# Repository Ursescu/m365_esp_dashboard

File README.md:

# M365 Dashboard replacement

## Description

Replacement for BLE m365 scooter dashboard using ESP32 chip.

## Build

Clone official esp-idf sdk repo and set `IDF_PATH` environment variable
to point it.

```bash
    git clone --recursive https://github.com/espressif/esp-idf.git ~/esp-idf

    cd ~/esp-idf && ./install.sh && . ./export.sh
```

Build app and watch the info using `make`.

```bash
    make flash monitor
```

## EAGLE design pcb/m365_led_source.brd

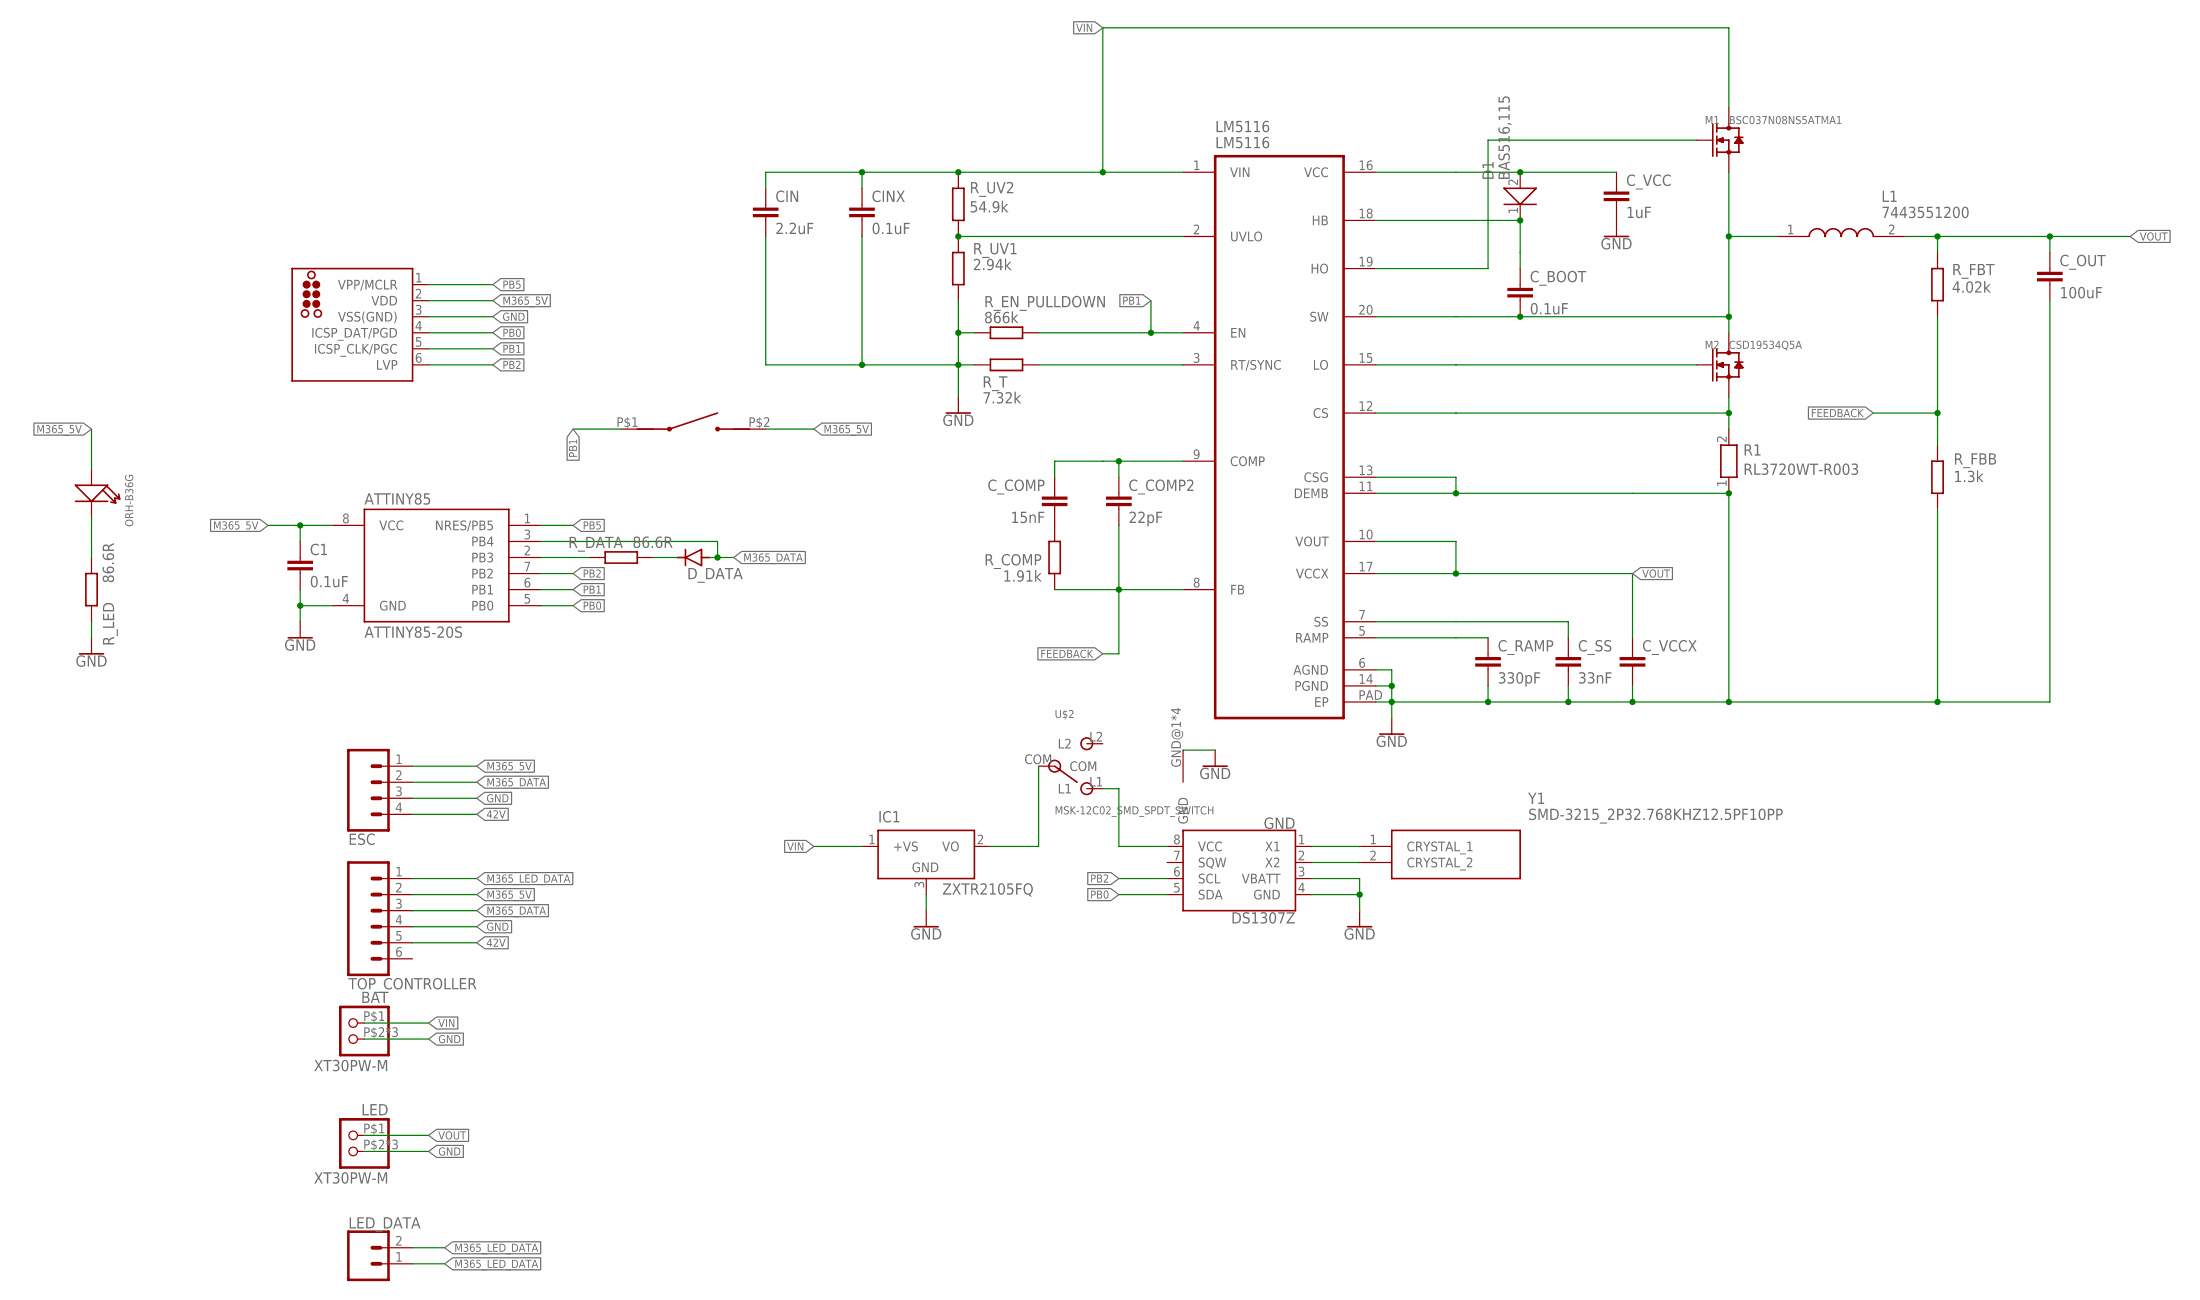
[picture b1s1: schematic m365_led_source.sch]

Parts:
ATTINY85: ATTINY85-20S; SOIC8_EIAJ_208MIL
BAT: XT30PW-M
C1: 0.1uF; C0402
CIN: 2.2uF; C1210
CINX: 0.1uF; C0603
C_BOOT: 0.1uF; C0603
C_COMP: 15nF; C1005
C_COMP2: 22pF; C0402
C_OUT: 100uF; C1210
C_RAMP: 330pF; C0402
C_SS: 33nF; C0402
C_VCC: 1uF; C0402
C_VCCX: CC0402; C0402
D1: BAS516,115; SOD1608X65N
D_DATA: SMAFJ75A
ESC: CONN_04LONGPADS; 1X04_LONGPADS
GND: DS1307Z; SO08-0.15
IC1: ZXTR2105FQ; SOT23
J2: TC2030-MCP-NL
L1: 7443551200; WE-HCI_1350/136523
LED: XT30PW-M
LED_DATA: CONN_02PTH3; 1X02_LONGPADS
LM5116: LM5116; TSSOP20-PAD
M1: BSC037N08NS5ATMA1; CSD19531Q5AT
M2: CSD19534Q5A; CSD19531Q5AT
R1: RL3720WT-R003; RESC2038X70N
R_COMP: 1.91k; R0402
R_DATA: 86.6R; R0402
R_EN_PULLDOWN: 866k; R0402
R_FBB: 1.3k; R1206
R_FBT: 4.02k; R1206
R_LED: 86.6R; R0402
R_T: 7.32k; R0402
R_UV1: 2.94k; R0402
R_UV2: 54.9k; R0402
TINY_LED: ORH-B36G; LED-0603
TOP_CONTROLLER: CONN_06LONGPADS; 1X06_LONGPADS
U$1: TL3302BF260QJ
U$2: MSK-12C02_SMD_SPDT_SWITCH; MSK-12C02
Y1: SMD-3215_2P32.768KHZ12.5PF10PP; SMD3215_2P32768KHZ125PF10PPM

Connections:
5V_REG: IC1.2 (VO), U$2.COM
42V: ESC.4, TOP_CONTROLLER.5
FEEDBACK: C_COMP2.2, LM5116.8 (FB), R_COMP.1, R_FBB.2, R_FBT.1
GND: ATTINY85.4 (GND), BAT.P$2 (2), BAT.P$3 (2), BAT.P$4 (2), C1.2, CIN.2, CINX.2, C_OUT.2, C_RAMP.2, C_SS.2, C_VCC.2, C_VCCX.2, ESC.3, GND.3 (VBATT), GND.4 (GND), IC1.3 (GND), J2.3 (VSS(GND)), LED.P$2 (2), LED.P$3 (2), LED.P$4 (2), LM5116.6 (AGND), LM5116.11 (DEMB), LM5116.13 (CSG), LM5116.14 (PGND), LM5116.PAD (EP), R1.1, R_EN_PULLDOWN.1, R_FBB.1, R_LED.1, R_T.1, R_UV1.1, TOP_CONTROLLER.4, U$2.GND@1 (GND), U$2.GND@2 (GND), U$2.GND@3 (GND), U$2.GND@4 (GND)
M365_5V: ATTINY85.8 (VCC), C1.1, ESC.1, J2.2 (VDD), TINY_LED.+, TOP_CONTROLLER.2, U$1.P$2
M365_DATA: ATTINY85.3 (PB4), D_DATA.P$2 (ANODE), ESC.2, TOP_CONTROLLER.3
M365_LED_DATA: LED_DATA.1, LED_DATA.2, TOP_CONTROLLER.1
unnamed: C_COMP.2, R_COMP.2
unnamed: LM5116.2 (UVLO), R_UV1.2, R_UV2.1
unnamed: GND.8 (VCC), U$2.L1
unnamed: LM5116.3 (RT/SYNC), R_T.2
unnamed: C_COMP.1, C_COMP2.1, LM5116.9 (COMP)
unnamed: GND.1 (X1), Y1.1 (CRYSTAL_1)
unnamed: C_SS.1, LM5116.7 (SS)
unnamed: C_RAMP.1, LM5116.5 (RAMP)
unnamed: R_LED.2, TINY_LED.-
unnamed: D_DATA.P$1 (CATHODE), R_DATA.2
unnamed: GND.2 (X2), Y1.2 (CRYSTAL_2)
unnamed: LM5116.12 (CS), M2.1 (S), M2.2 (S), M2.3 (S), R1.2
unnamed: LM5116.15 (LO), M2.4 (G)
unnamed: C_BOOT.2, L1.1, LM5116.20 (SW), M1.1 (S), M1.2 (S), M1.3 (S), M2.5 (D), M2.6 (D), M2.7 (D), M2.8 (D), M2.9 (D)
unnamed: LM5116.19 (HO), M1.4 (G)
unnamed: C_BOOT.1, D1.1, LM5116.18 (HB)
unnamed: C_VCC.1, D1.2, LM5116.16 (VCC)
PB0: ATTINY85.5 (PB0), GND.5 (SDA), J2.4 (ICSP_DAT/PGD)
PB1: ATTINY85.6 (PB1), J2.5 (ICSP_CLK/PGC), LM5116.4 (EN), R_EN_PULLDOWN.2, U$1.P$1
PB2: ATTINY85.7 (PB2), GND.6 (SCL), J2.6 (LVP)
PB3: ATTINY85.2 (PB3), R_DATA.1
PB5: ATTINY85.1 (NRES/PB5), J2.1 (VPP/MCLR)
VIN: BAT.P$1 (1), CIN.1, CINX.1, IC1.1 (+VS), LM5116.1 (VIN), M1.5 (D), M1.6 (D), M1.7 (D), M1.8 (D), M1.9 (D), R_UV2.2
VOUT: C_OUT.1, C_VCCX.1, L1.2, LED.P$1 (1), LM5116.10 (VOUT), LM5116.17 (VCCX), R_FBT.2

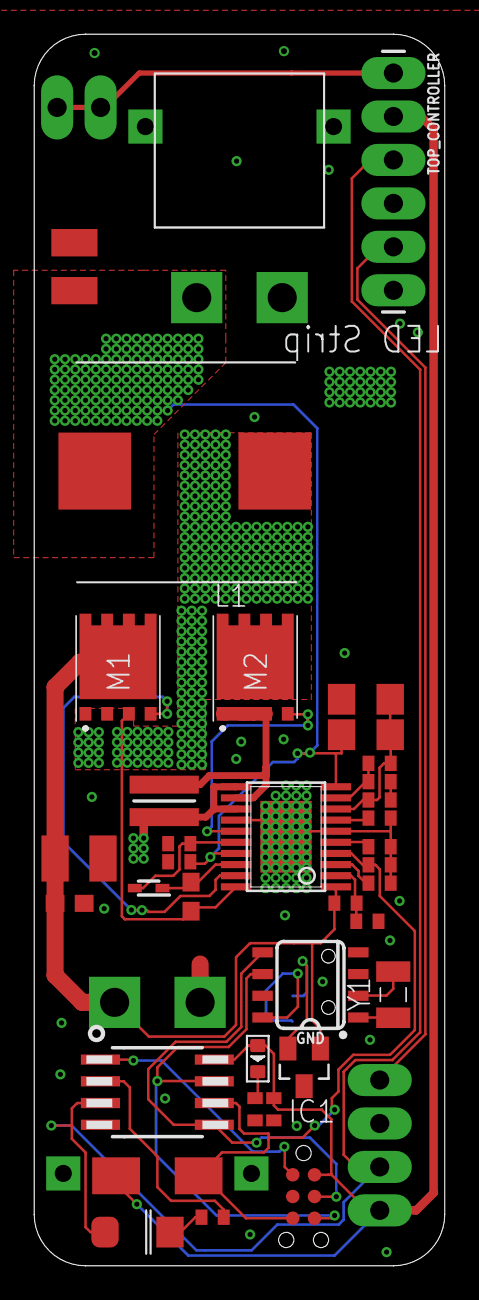
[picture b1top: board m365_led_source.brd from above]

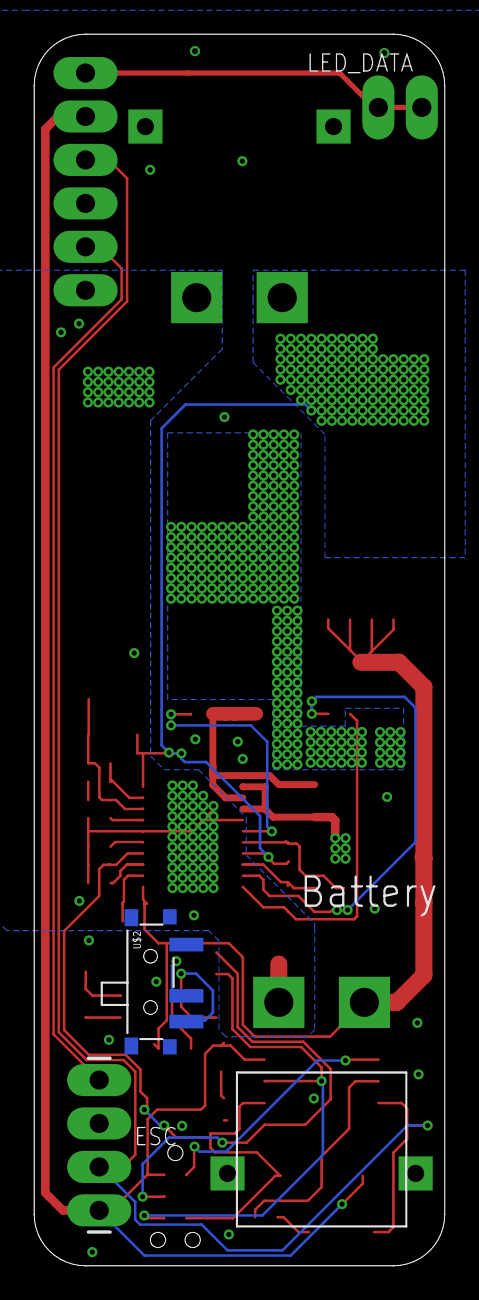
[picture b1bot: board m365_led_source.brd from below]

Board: 2 copper layers, 24.0 x 72.0 mm, 40 parts (4 on the bottom side), 31 nets.

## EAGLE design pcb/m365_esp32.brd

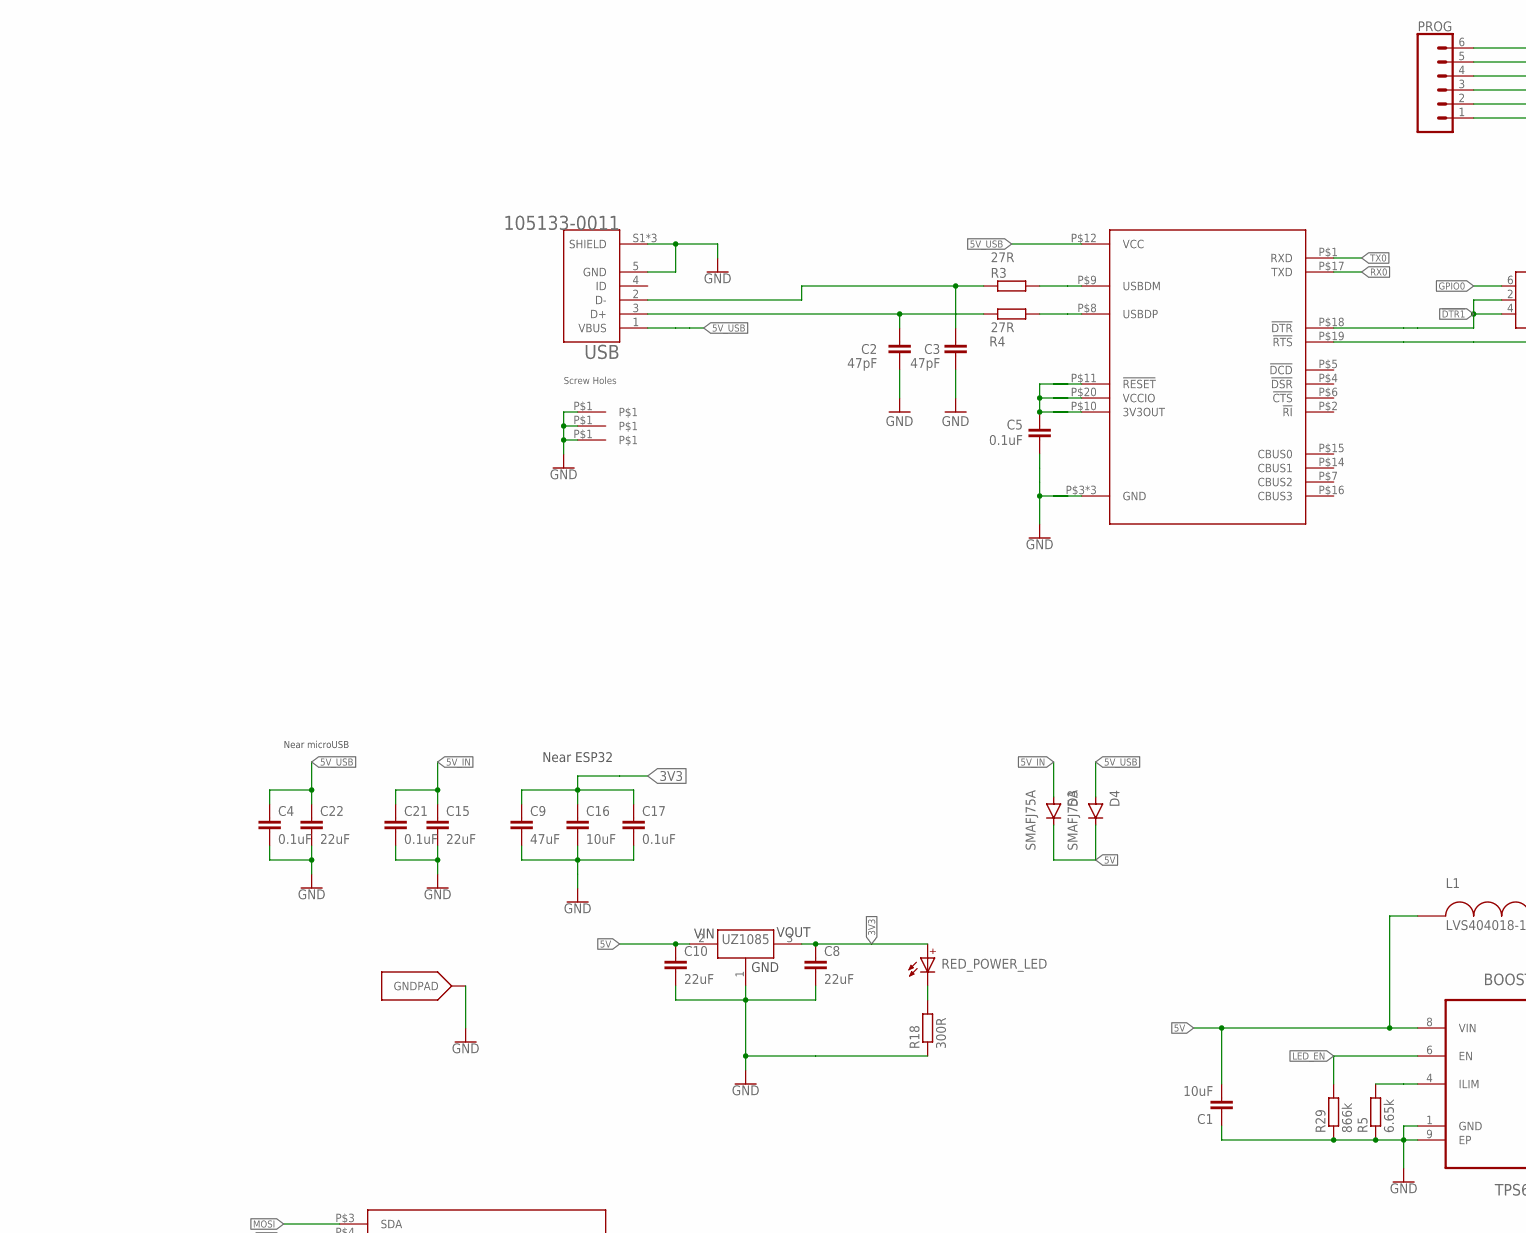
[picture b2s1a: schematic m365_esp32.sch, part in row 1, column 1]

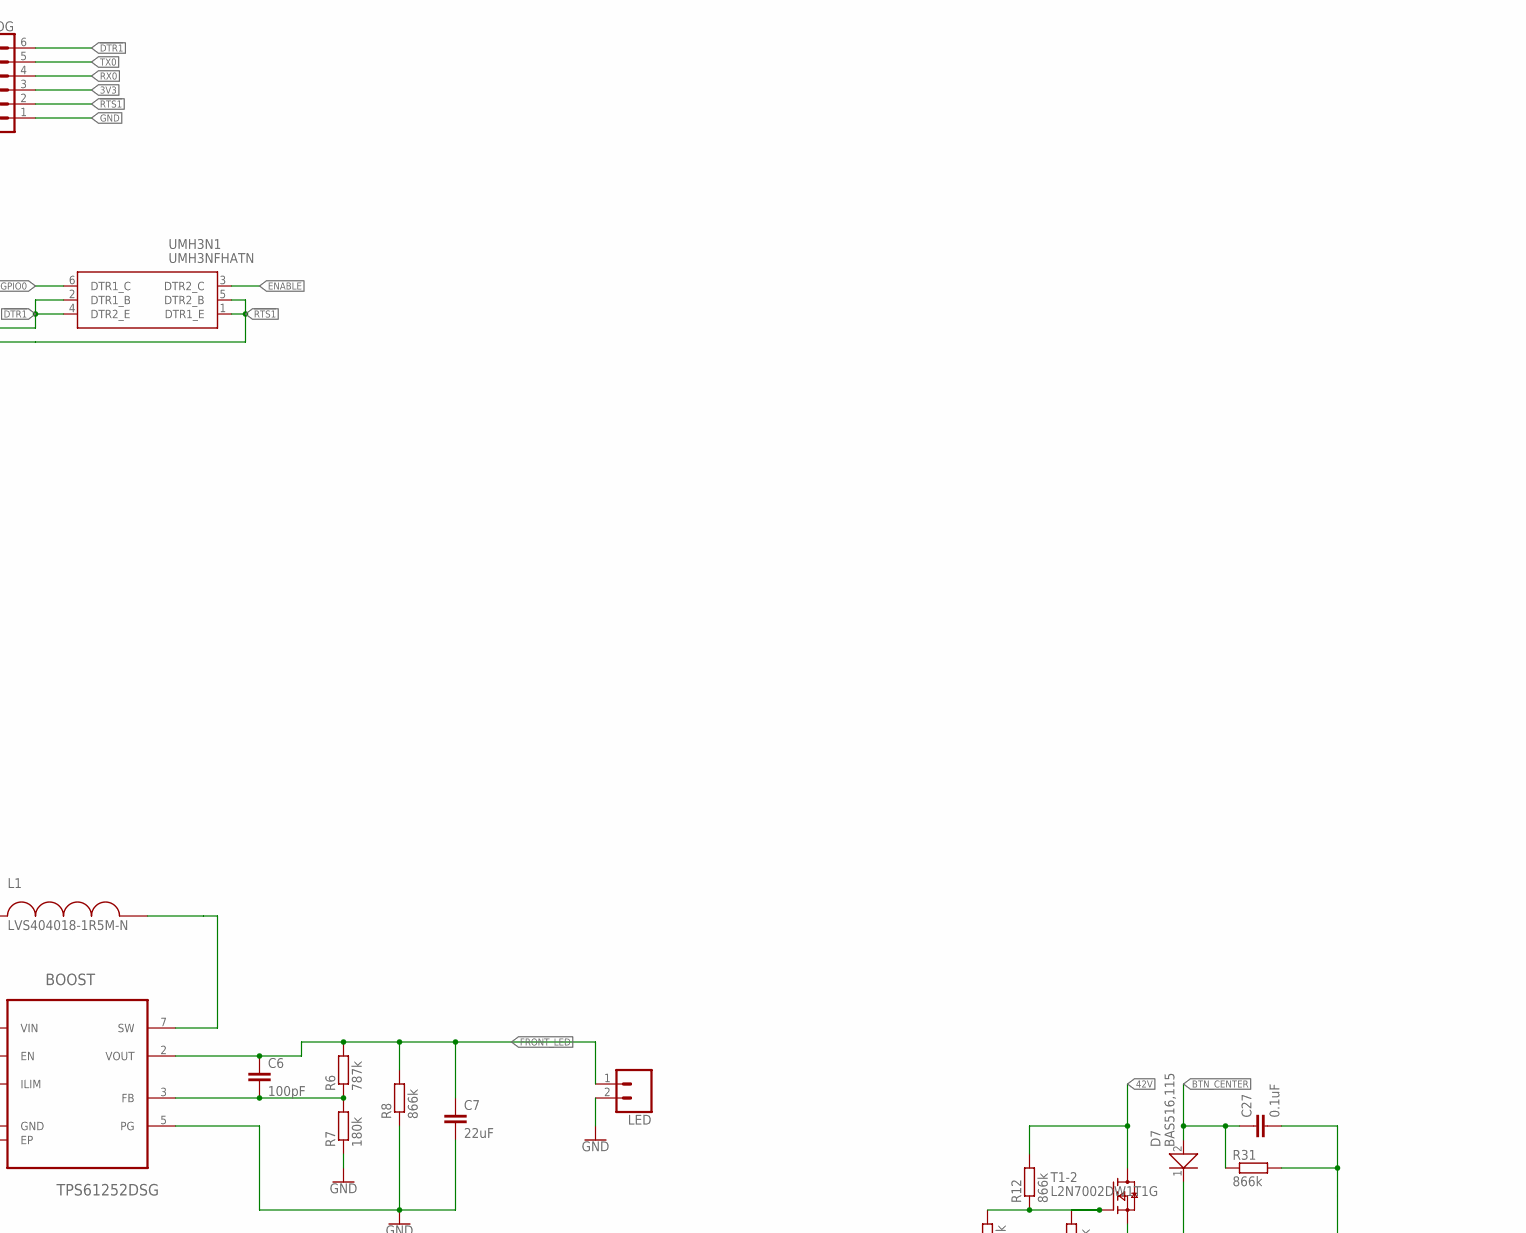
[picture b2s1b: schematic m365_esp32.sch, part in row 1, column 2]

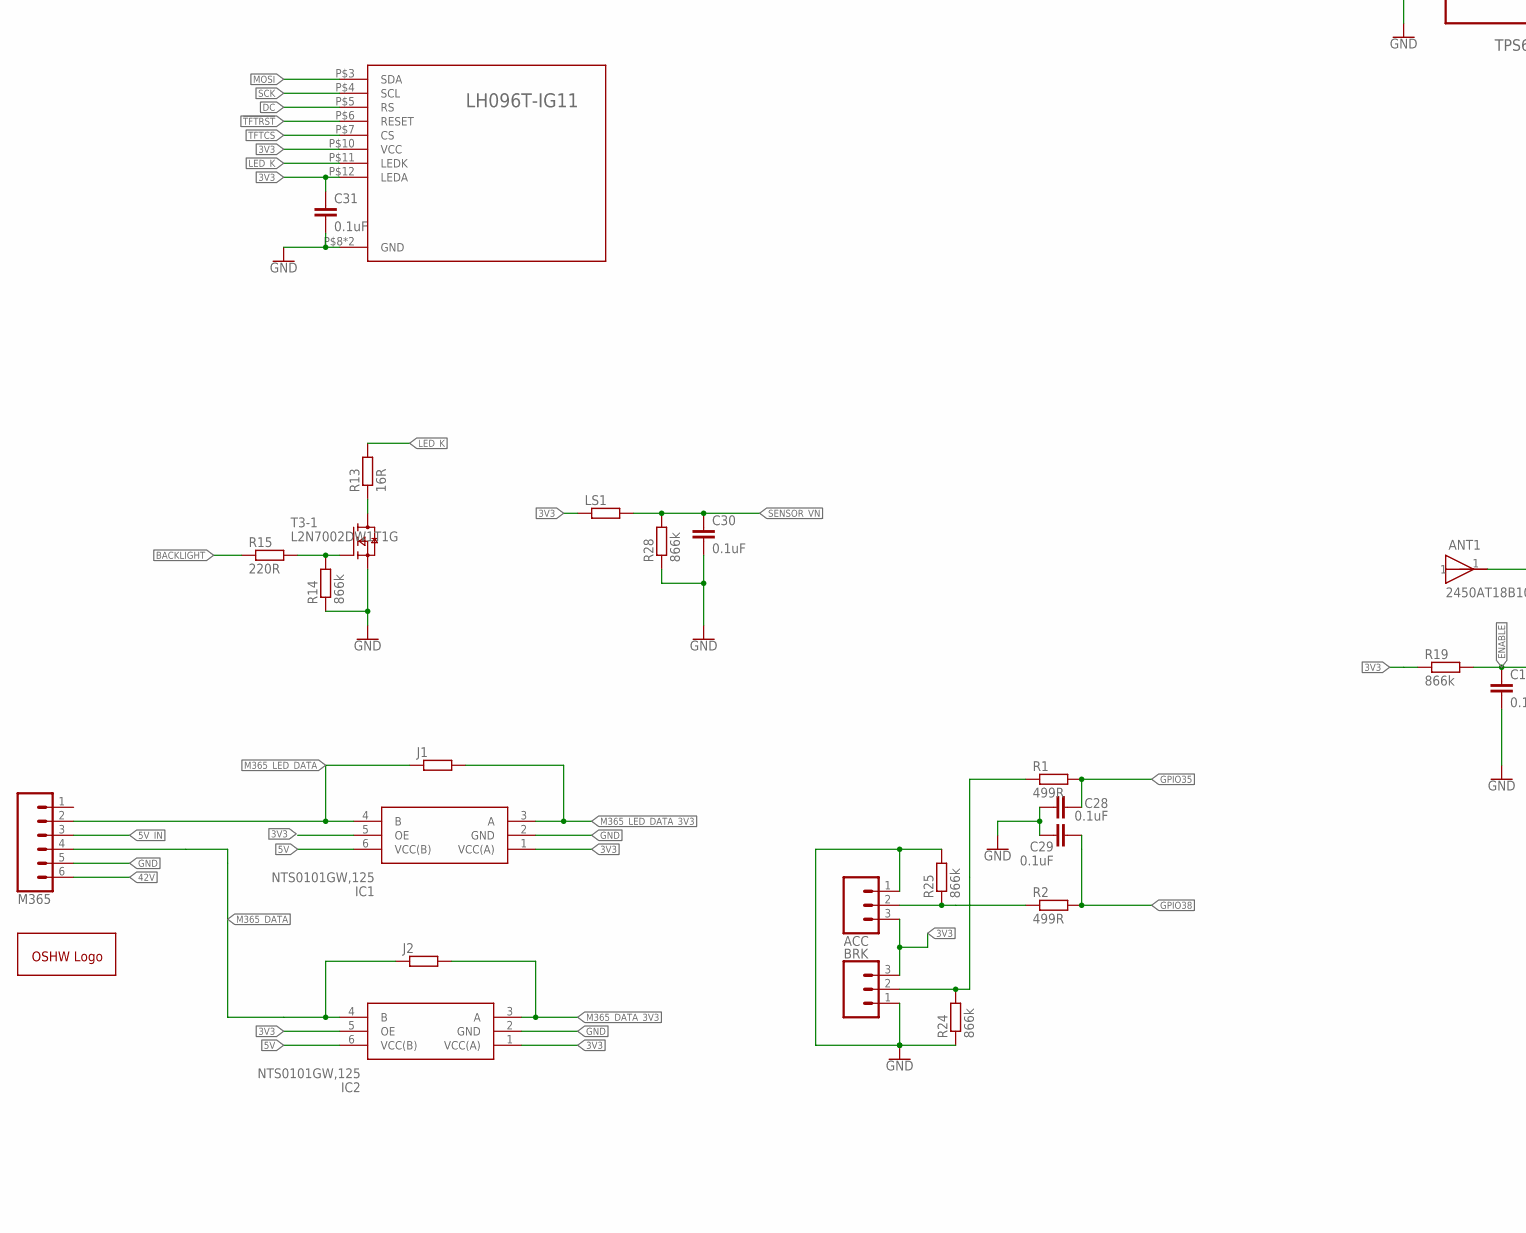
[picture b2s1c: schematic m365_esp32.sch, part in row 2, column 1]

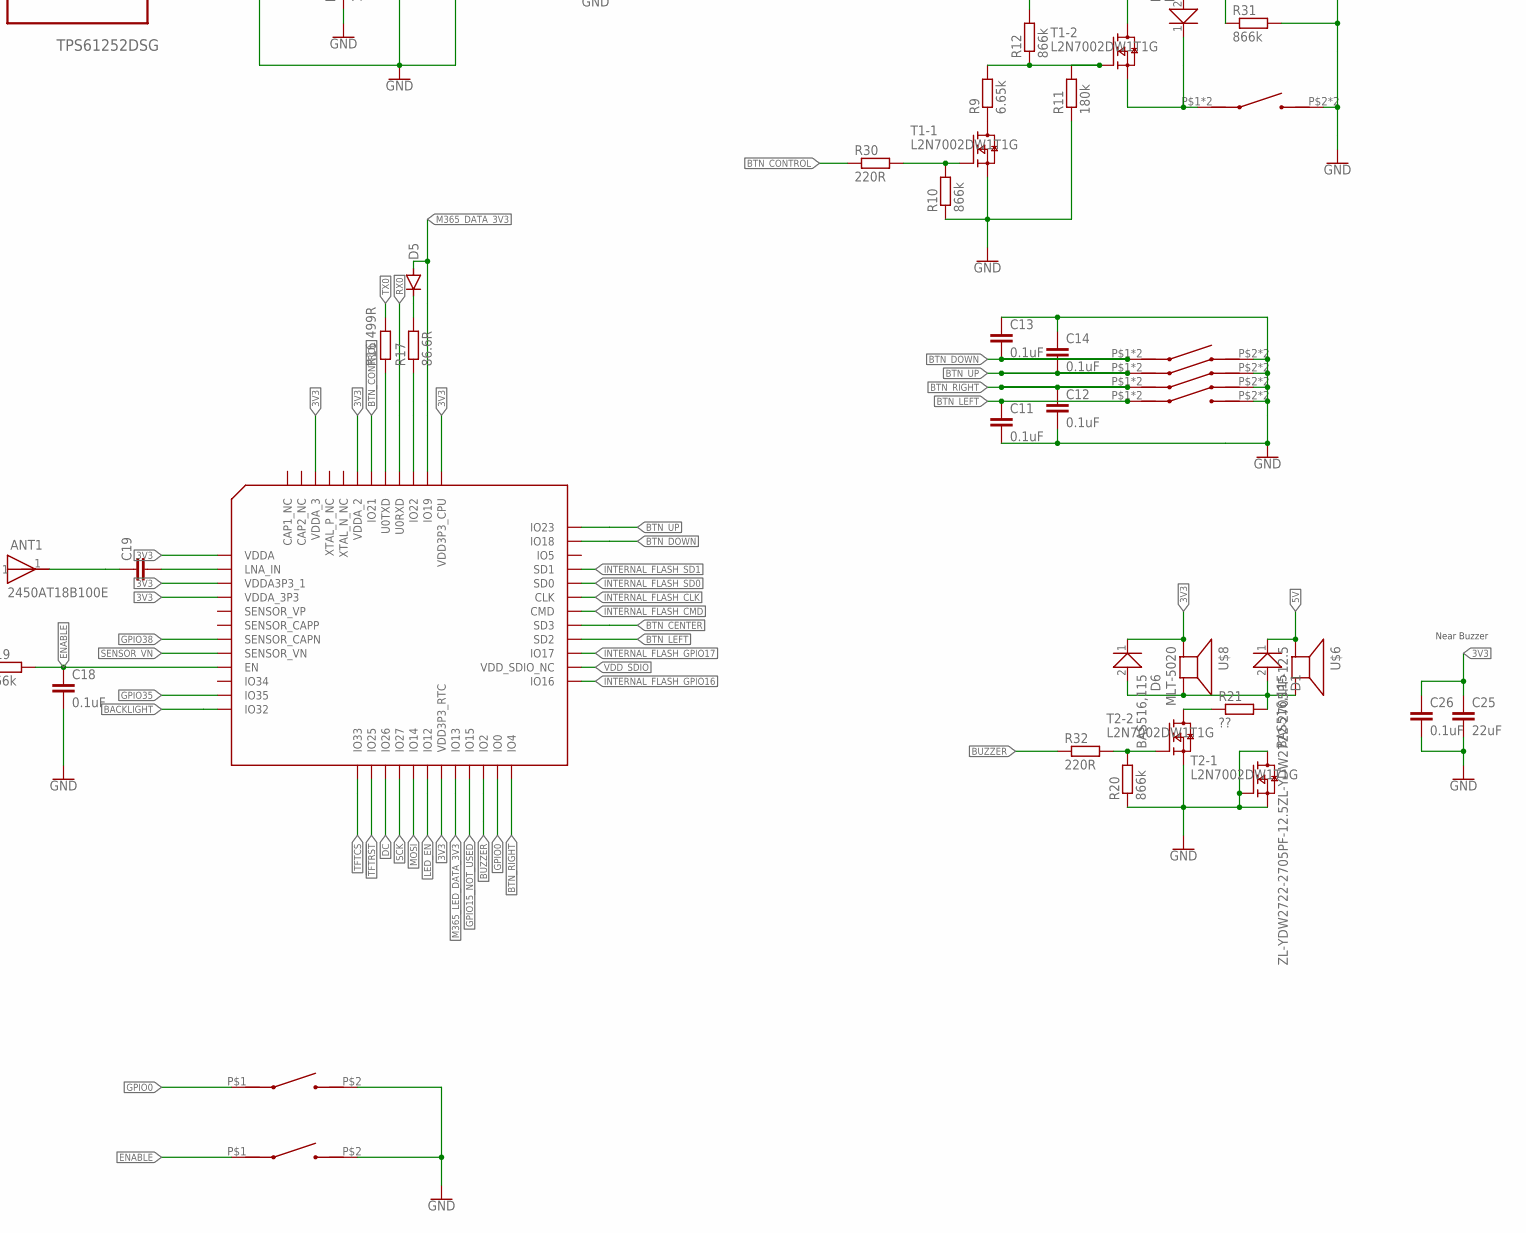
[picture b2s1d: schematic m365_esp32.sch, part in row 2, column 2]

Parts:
ACC: CONN_03LONGPADS; 1X03_LONGPADS
ANT1: 2450AT18B100E; ANT_2450AT18B100E
BOOST: TPS61252DSG; SON50P200X200X80-9N
BRK: CONN_03LONGPADS; 1X03_LONGPADS
C1: 10uF; C1206
C2, C3: 47pF; C0402
C4, C5, C11, C12, C13, C14, C17, C18, C21, C26, C27, C28, C29, C30, C31: 0.1uF; C0402
C6: 100pF; C0603
C7, C8, C10, C15, C22, C25: 22uF; C0603
C9: 47uF; C0603
C16: 10uF; C0402
C19: CC0402; C0402
CENTER: KSEK43J
D1, D6, D7: BAS516,115; SOD1608X65N
D3, D4, D5: SMAFJ75A
DOWN: KSEK43J
FT231X: FT231XQ-R
GOLD_ORB_SM2: OSHWLOGOLOGO5MM; OSHW_5MM
IC1, IC2: NTS0101GW,125; SOT65P210X110-6N
IC3: UNEXPECTEDMAKER_ESP32-PICO-D4; UNEXPECTEDMAKER_PICO-D4-QFN48
J1, J2: RR0402; R0402
L1: LVS404018-1R5M-N; LVS404018
LED: CONN_02PTH3; 1X02_LONGPADS
LEFT: KSEK43J
LS1: RR1206; R1206
M365: CONN_06LONGPADS; 1X06_LONGPADS
PROG: CONN_06LOCK; 1X06_LOCK
R1, R2, R16: 499R; R0402
R3, R4: 27R; R0402
R5, R9: 6.65k; R0402
R6: 787k; R0603
R7, R11: 180k; R0603
R8, R10, R12, R14, R19, R20, R24, R25, R28, R29, R31: 866k; R0402
R13: 16R; R0402
R15, R30, R32: 220R; R0402
R17: 86.6R; R0402
R18: 300R; R0402
R21: ??; R0805
RED_POWER_LED: WL-SMCD_0603_150060BS55040; WL-SMCD_0603
REG: UZ1085L-33-TN3-R; TO-252-2
RIGHT: KSEK43J
T1, T2, T3: L2N7002DW1T1G; SOT363
U$1, U$2: TL3302BF260QJ
U$3, U$4, U$5: SCREWHOLE-M2
U$6: ZL-YDW2722-2705PF-12.5ZL-YDW2722-2705PF-12.5; ZL-YDW2722-2705PF-12.5
U$8: MLT-5020
U$11: LH096T-IG11
UMH3N1: UMH3NFHATN; SOT65P210X100-6N
UP: KSEK43J
USB: 105133-0011; MOLEX_105133-0011

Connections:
3V3: ACC.3, BRK.3, C8.1, C9.1, C16.1, C17.1, C25.1, C26.1, C31.1, D6.1, IC1.1 (VCC(A)), IC1.5 (OE), IC2.1 (VCC(A)), IC2.5 (OE), IC3.1 (VDDA), IC3.3 (VDDA3P3_1), IC3.4 (VDDA_3P3), IC3.19 (VDD3P3_RTC), IC3.37 (VDD3P3_CPU), IC3.43 (VDDA_2), IC3.46 (VDDA_3), LS1.1, PROG.3, R19.1, RED_POWER_LED.2 (A), REG.3 (VOUT), U$8.P$2 (+), U$11.P$10 (VCC), U$11.P$12 (LEDA)
5V: BOOST.8 (VIN), C1.2, C10.1, D1.1, D3.P$1 (CATHODE), D4.P$1 (CATHODE), IC1.6 (VCC(B)), IC2.6 (VCC(B)), L1.P$1, REG.2 (VIN), U$6.P$1 (+)
5V_IN: C15.1, C21.1, D3.P$2 (ANODE), M365.3
5V_USB: C4.1, C22.1, D4.P$2 (ANODE), FT231X.P$12 (VCC), USB.1 (VBUS)
42V: M365.6, R12.2, T1.3 (D)
!DTR1: FT231X.P$18 (!DTR), PROG.6, UMH3N1.2 (DTR1_B), UMH3N1.4 (DTR2_E)
!RTS1: FT231X.P$19 (!RTS), PROG.2, UMH3N1.1 (DTR1_E), UMH3N1.5 (DTR2_B)
!TFTRST: IC3.14 (IO25), U$11.P$6 (RESET)
A2: ACC.2, R2.1, R25.1
A5: BRK.2, R1.1, R24.2
BACKLIGHT: IC3.12 (IO32), R15.1
BTN_CENTER: C27.1, D7.2, IC3.29 (SD3), R31.1
BTN_CONTROL: IC3.42 (IO21), R30.1
BTN_DOWN: C13.2, DOWN.P$1, DOWN.P$4, IC3.35 (IO18)
BTN_LEFT: C11.1, IC3.28 (SD2), LEFT.P$1, LEFT.P$4
BTN_RIGHT: C12.1, IC3.24 (IO4), RIGHT.P$1, RIGHT.P$4
BTN_UP: C14.2, IC3.36 (IO23), UP.P$1, UP.P$4
BUZZER: IC3.22 (IO2), R32.1
DC: IC3.15 (IO26), U$11.P$5 (RS)
ENABLE: C18.1, IC3.9 (EN), R19.2, U$2.P$1, UMH3N1.3 (DTR2_C)
FRONT_LED: BOOST.2 (VOUT), C6.1, C7.1, LED.1, R6.2, R8.2
GND: ACC.1, BOOST.1 (GND), BOOST.5 (PG), BOOST.9 (EP), BRK.1, C1.1, C2.1, C3.1, C4.2, C5.2, C7.2, C8.2, C9.2, C10.2, C11.2, C12.2, C13.1, C14.1, C15.2, C16.2, C17.2, C18.2, C21.2, C22.2, C25.2, C26.2, C27.2, C28.1, C29.1, C30.2, C31.2, CENTER.P$2, CENTER.P$3, DOWN.P$2, DOWN.P$3, FT231X.P$3 (GND), FT231X.P$13 (GND), FT231X.P$21 (GND), IC1.2 (GND), IC2.2 (GND), IC3.EXP (GNDPAD), LED.2, LEFT.P$2, LEFT.P$3, M365.5, PROG.1, R5.1, R7.1, R8.1, R10.1, R11.1, R14.1, R18.1, R20.1, R24.1, R25.2, R28.1, R29.1, R31.2, REG.1 (GND), RIGHT.P$2, RIGHT.P$3, T1.1 (S), T2.1 (S), T2.2 (G), T2.4 (S), T2.6 (D), T3.1 (S), U$1.P$2, U$2.P$2, U$3.P$1, U$4.P$1, U$5.P$1, U$11.P$8 (GND), U$11.P$13 (GND), UP.P$2, UP.P$3, USB.5 (GND), USB.S1 (SHIELD), USB.S2 (SHIELD), USB.S3 (SHIELD)
GPIO0: IC3.23 (IO0), U$1.P$1, UMH3N1.6 (DTR1_C)
GPIO15_NOT_USED: IC3.21 (IO15)
GPIO35: C28.2, IC3.11 (IO35), R1.2
GPIO38: C29.2, IC3.7 (SENSOR_CAPN), R2.2
INTERNAL_FLASH_CLK: IC3.31 (CLK)
INTERNAL_FLASH_CMD: IC3.30 (CMD)
INTERNAL_FLASH_GPIO16: IC3.25 (IO16)
INTERNAL_FLASH_GPIO17: IC3.27 (IO17)
INTERNAL_FLASH_SD0: IC3.32 (SD0)
INTERNAL_FLASH_SD1: IC3.33 (SD1)
LED_EN: BOOST.6 (EN), IC3.18 (IO12), R29.2
LED_K: R13.2, U$11.P$11 (LEDK)
LNA_IN: C19.2, IC3.2 (LNA_IN)
M365_DATA: IC2.4 (B), J2.1, M365.4
M365_DATA_3V3: D5.P$2 (ANODE), IC2.3 (A), IC3.38 (IO19), J2.2
M365_LED_DATA: IC1.4 (B), J1.1, M365.2
M365_LED_DATA_3V3: IC1.3 (A), IC3.20 (IO13), J1.2
MOSI: IC3.17 (IO14), U$11.P$3 (SDA)
unnamed: IC3.41 (U0TXD), R16.1
unnamed: ANT1.1, C19.1
unnamed: R18.2, RED_POWER_LED.1 (C)
unnamed: CENTER.P$1, CENTER.P$4, D7.1, T1.4 (S)
unnamed: R9.2, R11.2, R12.1, T1.5 (G)
unnamed: C5.1, FT231X.P$10 (3V3OUT), FT231X.P$11 (!RESET), FT231X.P$20 (VCCIO)
unnamed: BOOST.7 (SW), L1.P$2
unnamed: BOOST.4 (ILIM), R5.2
unnamed: BOOST.3 (FB), C6.2, R6.1, R7.2
unnamed: R9.1, T1.6 (D)
unnamed: D1.2, D6.2, R21.2, U$6.P$2 (-), U$8.P$3 (-)
unnamed: R21.1, T2.3 (D)
unnamed: R13.1, T3.6 (D)
unnamed: R14.2, R15.2, T3.2 (G)
unnamed: D5.P$1 (CATHODE), R17.2
unnamed: IC3.39 (IO22), R17.1
unnamed: R10.2, R30.2, T1.2 (G)
unnamed: R20.2, R32.2, T2.5 (G)
RX0: FT231X.P$17 (TXD), IC3.40 (U0RXD), PROG.4
SCK: IC3.16 (IO27), U$11.P$4 (SCL)
SENSOR_VN: C30.1, IC3.8 (SENSOR_VN), LS1.2, R28.2
TFTCS: IC3.13 (IO33), U$11.P$7 (CS)
TX0: FT231X.P$1 (RXD), PROG.5, R16.2
USB-DATA_M: C3.2, R3.1, USB.2 (D-)
USB-DATA_P: C2.2, R4.1, USB.3 (D+)
USBDM: FT231X.P$9 (USBDM), R3.2
USBDP: FT231X.P$8 (USBDP), R4.2
VDD_SDIO: IC3.26 (VDD_SDIO_NC)

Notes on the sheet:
Near ESP32
Screw Holes
Near Buzzer
Near microUSB

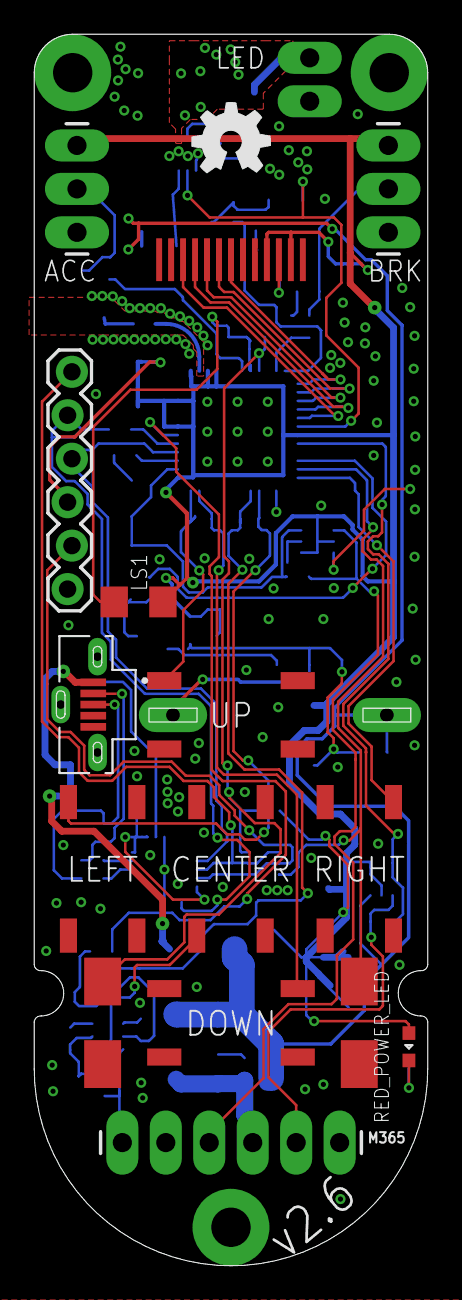
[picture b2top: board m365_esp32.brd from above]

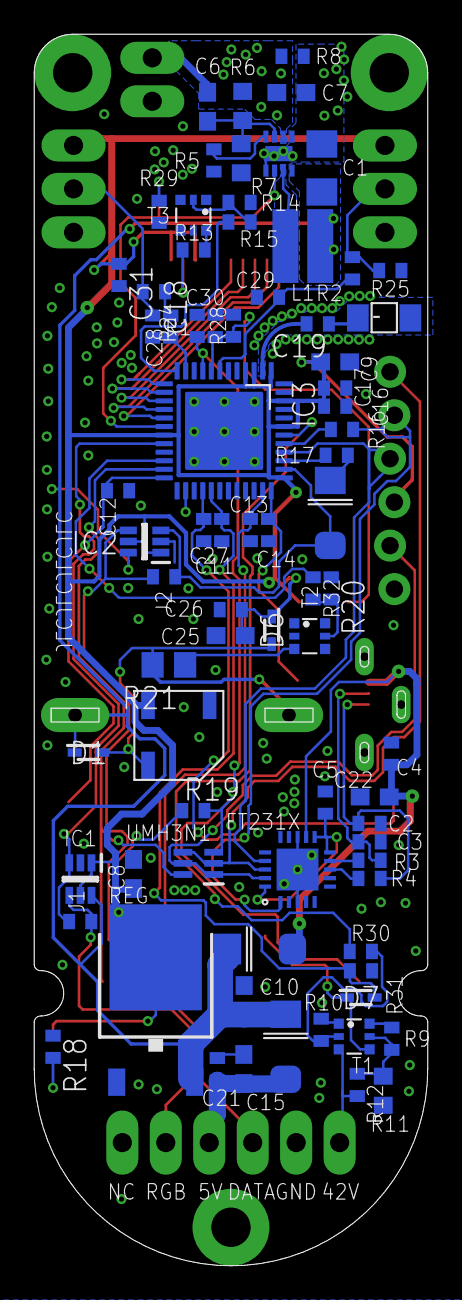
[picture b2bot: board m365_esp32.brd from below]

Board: 2 copper layers, 23.0 x 72.0 mm, 98 parts (77 on the bottom side), 60 nets.

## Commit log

2019-09-21 Removed old sdkconfig
2019-09-21 Added .clang-format file
2019-09-21 Auto-format
2019-09-21 Added LICENSE file
2019-09-21 Do not use cmake, use just make
2019-09-21 Moved to `main` folder
2019-09-21 Changed the project name
2019-09-25 Added more functionality in comm subsys
2019-09-25 Added message types to be sent to the controller
2019-09-25 Refactored
2019-09-25 TMP: Make connection stable
2019-10-01 proto: Added stat structure that objectify the current state.
2019-10-01 proto: Added function that verifies the CRC of message
2019-10-01 proto: Early implementation of process command function
2019-10-02 FIX: proto: Now can read more commands from buffer. utils: Debug variable not used properly. adc: Dummy speed values to test the application comm: Relaxed TX_INTERVAL and RX_TIMEOUT Build errors.
2019-10-11 proto: Fix process command offsets
2019-10-13 Added first version of the pcb design
2019-10-13 Added oshpark's pcb render
2019-10-13 Placed the buttons, center button multiplexer, usb interface, 3v3 regulator
2019-10-14 Finished placing all components on the board
2019-10-15 proto: Refactoring comments, removed commented code and moved state debug in explicit function
2019-10-15 buzzer: Added function definitions for buzzer and integrated in proto.c
2019-11-25 Added secondary pcb to supply power for RGB led strip
2019-11-25 Finished dashboard PCB
2019-12-15 Added display.c
2019-12-15 Migrated project to esp-idf v4 and CMake
2019-12-15 Added ESP32_TFT submodule
2019-12-15 Moved component files to /components.
2019-12-15 Use Kconfig variables
2019-12-15 Use Kconfig variables for M365 pins and constants
2019-12-16 Fixed display requirements
2019-12-16 Added basic adc reads
2019-12-16 Added acceleration and brake sensor Kconfig options
2019-12-16 Fixed ADC read
2019-12-16 Auto-formatted all files
2019-12-16 Start all tasks
2019-12-16 Added buzzer feature
2019-12-16 Implemented acceleration&brake adc auto ranging
2019-12-16 Added Kconfig Buzzer variables
2019-12-16 Fix beep package handling
2019-12-16 When beeping stops, make the GPIO high
2019-12-16 Better handle the channel stop
2019-12-28 Added basic ws2812 led strip functionality
2020-01-10 Added preferences save&load features
2020-01-10 Added esp log functions
2020-01-14 Added test code
2020-01-31 Updated dashboard PCB design. Replaced ESP32-D0DW with ESP32-PicoD4 Added bigger buzzer footprint Removed RGB led
2020-01-31 Updated led source board. Added RTC chip + regulator for it Changed the pinout of the attiny45 so that it can be programmed in place
2020-03-01 Modified TFT library to make it work with our 0.96" display
2020-03-01 Complete the display setup code and added a basic demo screen
2020-03-01 Added minimal preference saving to non volatile storage.
2020-03-01 Aligned every file to the naming convention.
2020-03-01 Added esp_log.h for ESP_LOG defines.
2020-03-02 Fixed ESP32_TFT submodule source URL.
2020-03-02 Fixed some typos, moved from printf to ESP_LOG.
2020-03-16 Use ESP_LOG instead of printf
2020-03-16 Added field names to default_preferences
2020-03-16 Barebones sketch for attiny85 that tests the buck converter for the RGB LED strip.
2020-03-16 Removed old, unused file: backup.ino
2020-03-16 Modified sdkconfig to use custom PCB's GPIO
2020-03-16 Basic wifi setup
2020-03-16 Display screens
2020-03-16 Added spiffs support for bmp images
2020-03-16 Set SPI Flash size to 4MB
2020-03-16 Replace int variable declarations with uint8_t
2020-03-16 Added extern proto_mainboard_stats
2020-03-16 Added rabbit, turtle and skull bmp images
2020-03-16 Set CPU frequency to 240Mhz
2020-03-16 Moved GET_TIME() from proto to utils
2020-03-16 Removed display_queue
2020-03-16 Added GPIO for front led and center button control
2020-03-16 Implemented barebones display of speed and battery stats
2020-03-16 Fix: forgot to remove display_queue from proto.h
2020-03-16 Fix ESP_LOG errors
2020-03-16 Fix: rename display functions to adhere to naming convention
2020-03-16 Changed demo font to DotMatrix.fon
2020-03-16 Fix: git, please behave!

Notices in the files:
parts and their libraries:
SparkFun-Connectors: Licensing: Creative Commons ShareAlike 4.0 International - https://creativecommons.org/licenses/by-sa/4.0
Wurth_Elektronik_Optoelectronics_rev18a: Copyright: Würth Elektronik
tag-connect: ©2009 ROFA.cz - modified and updated by Robert Darlington ‹rdarlington@gmail.com›
